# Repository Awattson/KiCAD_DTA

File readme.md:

# KiCAD設計TA

回路設計における知識と技能を競いながら学びましょう．

---

## TA_01
[ATtiny402](https://akizukidenshi.com/goodsaffix/ATtiny202-204-402-404-406-DataSheet-DS40002318A.pdf)で[NeoPixel](https://akizukidenshi.com/goodsaffix/WS2812B_20200225.pdf)を3つ光らせる基板です．
ATtiny402には，NeoPixelを光らせる指令を受け取るためのUART(USART)と，プログラムを書き込むためのUPDIを取り付けましょう．

条件

    ・配線は1層のみ（リード部品の反転可）
    ・NeoPixelの電源はUSB typeC
    ・ATtinyはマイコン間通信用のUARTを用意すること
    ・基板外形の最大寸法は40x40mm^2
    ・タイマースタートはプロジェクトのSCHを開いた瞬間
    ・タイマーストップはJLCPCB用の製造ファイルをZipにまとめた瞬間

### 資料

### サンプル画像

---

## インストール方法

```bash
git clone https://github.com/Awattson/KiCAD_DTA.git
mkdir username_TA_01
cd username_TA_01
# KiCADのプロジェクトを作成して始めましょう

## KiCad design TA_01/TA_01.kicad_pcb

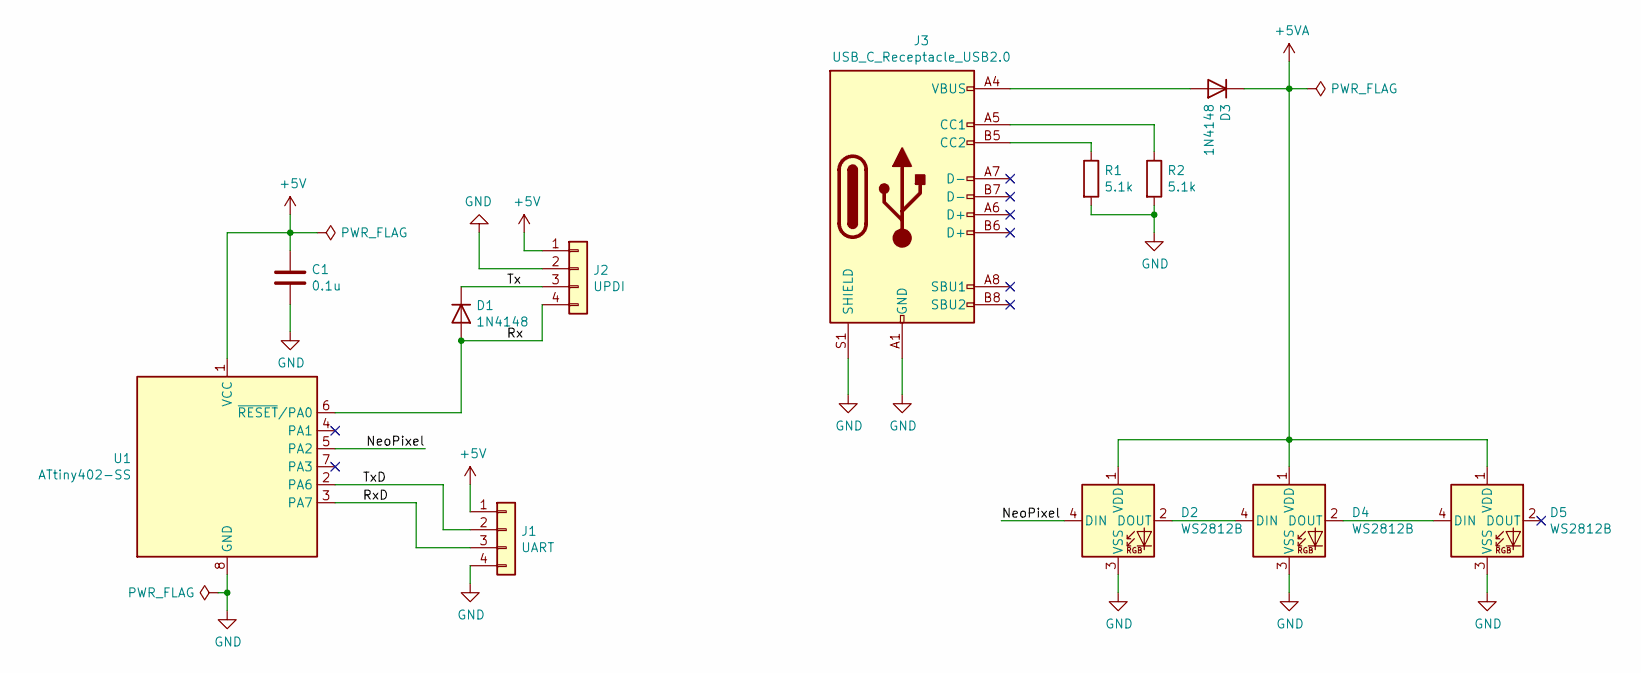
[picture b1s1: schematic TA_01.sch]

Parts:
C1: 0.1u; C_0603_1608Metric
D1, D3: 1N4148; D_DO-35_SOD27_P7.62mm_Horizontal
D2, D4, D5: WS2812B; LED_WS2812B_PLCC4_5.0x5.0mm_P3.2mm
J1: UART; JST_XH_S4B-XH-A-1_1x04_P2.50mm_Horizontal
J2: UPDI; JST_XH_S4B-XH-A-1_1x04_P2.50mm_Horizontal
J3: USB_C_Receptacle_USB2.0; USB_C_Receptacle_Palconn_UTC16-G
R1, R2: 5.1k; R_1206_3216Metric
U1: ATtiny402-SS; SOIC-8_3.9x4.9mm_P1.27mm

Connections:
+5V: C1.1, J1.1, J2.1, U1.1 (VCC)
+5VA: D2.1 (VDD), D3.1 (K), D4.1 (VDD), D5.1 (VDD)
/NeoPixel: D2.4 (DIN), U1.5 (PA2)
/Rx: D1.2 (A), J2.4, U1.6 (~RESET~/PA0)
/RxD: J1.3, U1.3 (PA7)
/Tx: D1.1 (K), J2.3
/TxD: J1.2, U1.2 (PA6)
GND: C1.2, D2.3 (VSS), D4.3 (VSS), D5.3 (VSS), J1.4, J2.2, J3.A1 (GND), J3.A12 (GND), J3.B1 (GND), J3.B12 (GND), J3.S1 (SHIELD), R1.2, R2.2, U1.8 (GND)
unnamed: D2.2 (DOUT), D4.4 (DIN)
unnamed: D3.2 (A), J3.A4 (VBUS), J3.A9 (VBUS), J3.B4 (VBUS), J3.B9 (VBUS)
unnamed: D4.2 (DOUT), D5.4 (DIN)
unnamed: J3.A5 (CC1), R2.1
unnamed: J3.B5 (CC2), R1.1

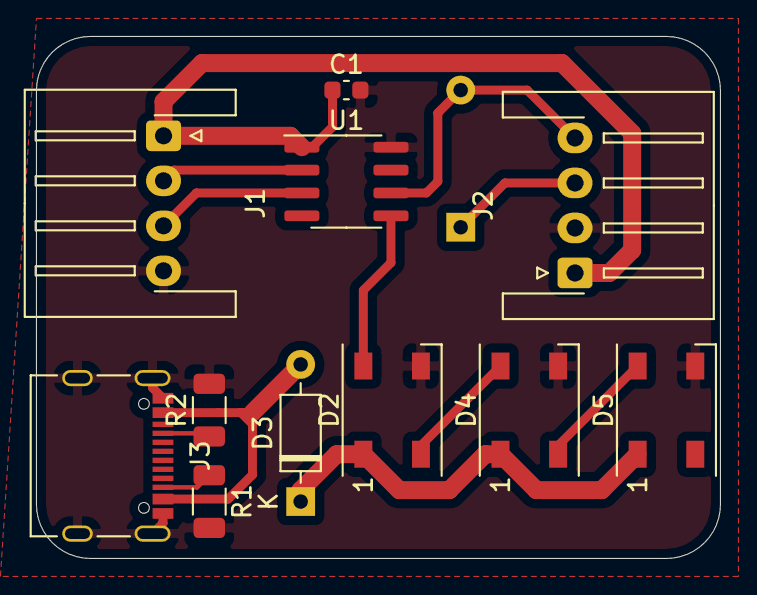
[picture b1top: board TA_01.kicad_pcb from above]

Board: 2 copper layers, 38.0 x 29.0 mm, 12 parts (1 on the bottom side), 13 nets.

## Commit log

2025-08-19 init
2025-08-19 add LICENSE
2025-08-19 created readme
2025-08-19 upgrade
2025-08-19 rule was updated
